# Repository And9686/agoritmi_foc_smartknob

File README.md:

# Algoritmi SmartKnob DevKit
## Motivation
This repository intends to achieve a development kit for a SmartKnob like the one from scottbez and allow it to be compatible with any microcontroller with dedicated firmware adaptable to any board. This DevKit design is inspired by NanoFoc DevKit by KatBinaris.

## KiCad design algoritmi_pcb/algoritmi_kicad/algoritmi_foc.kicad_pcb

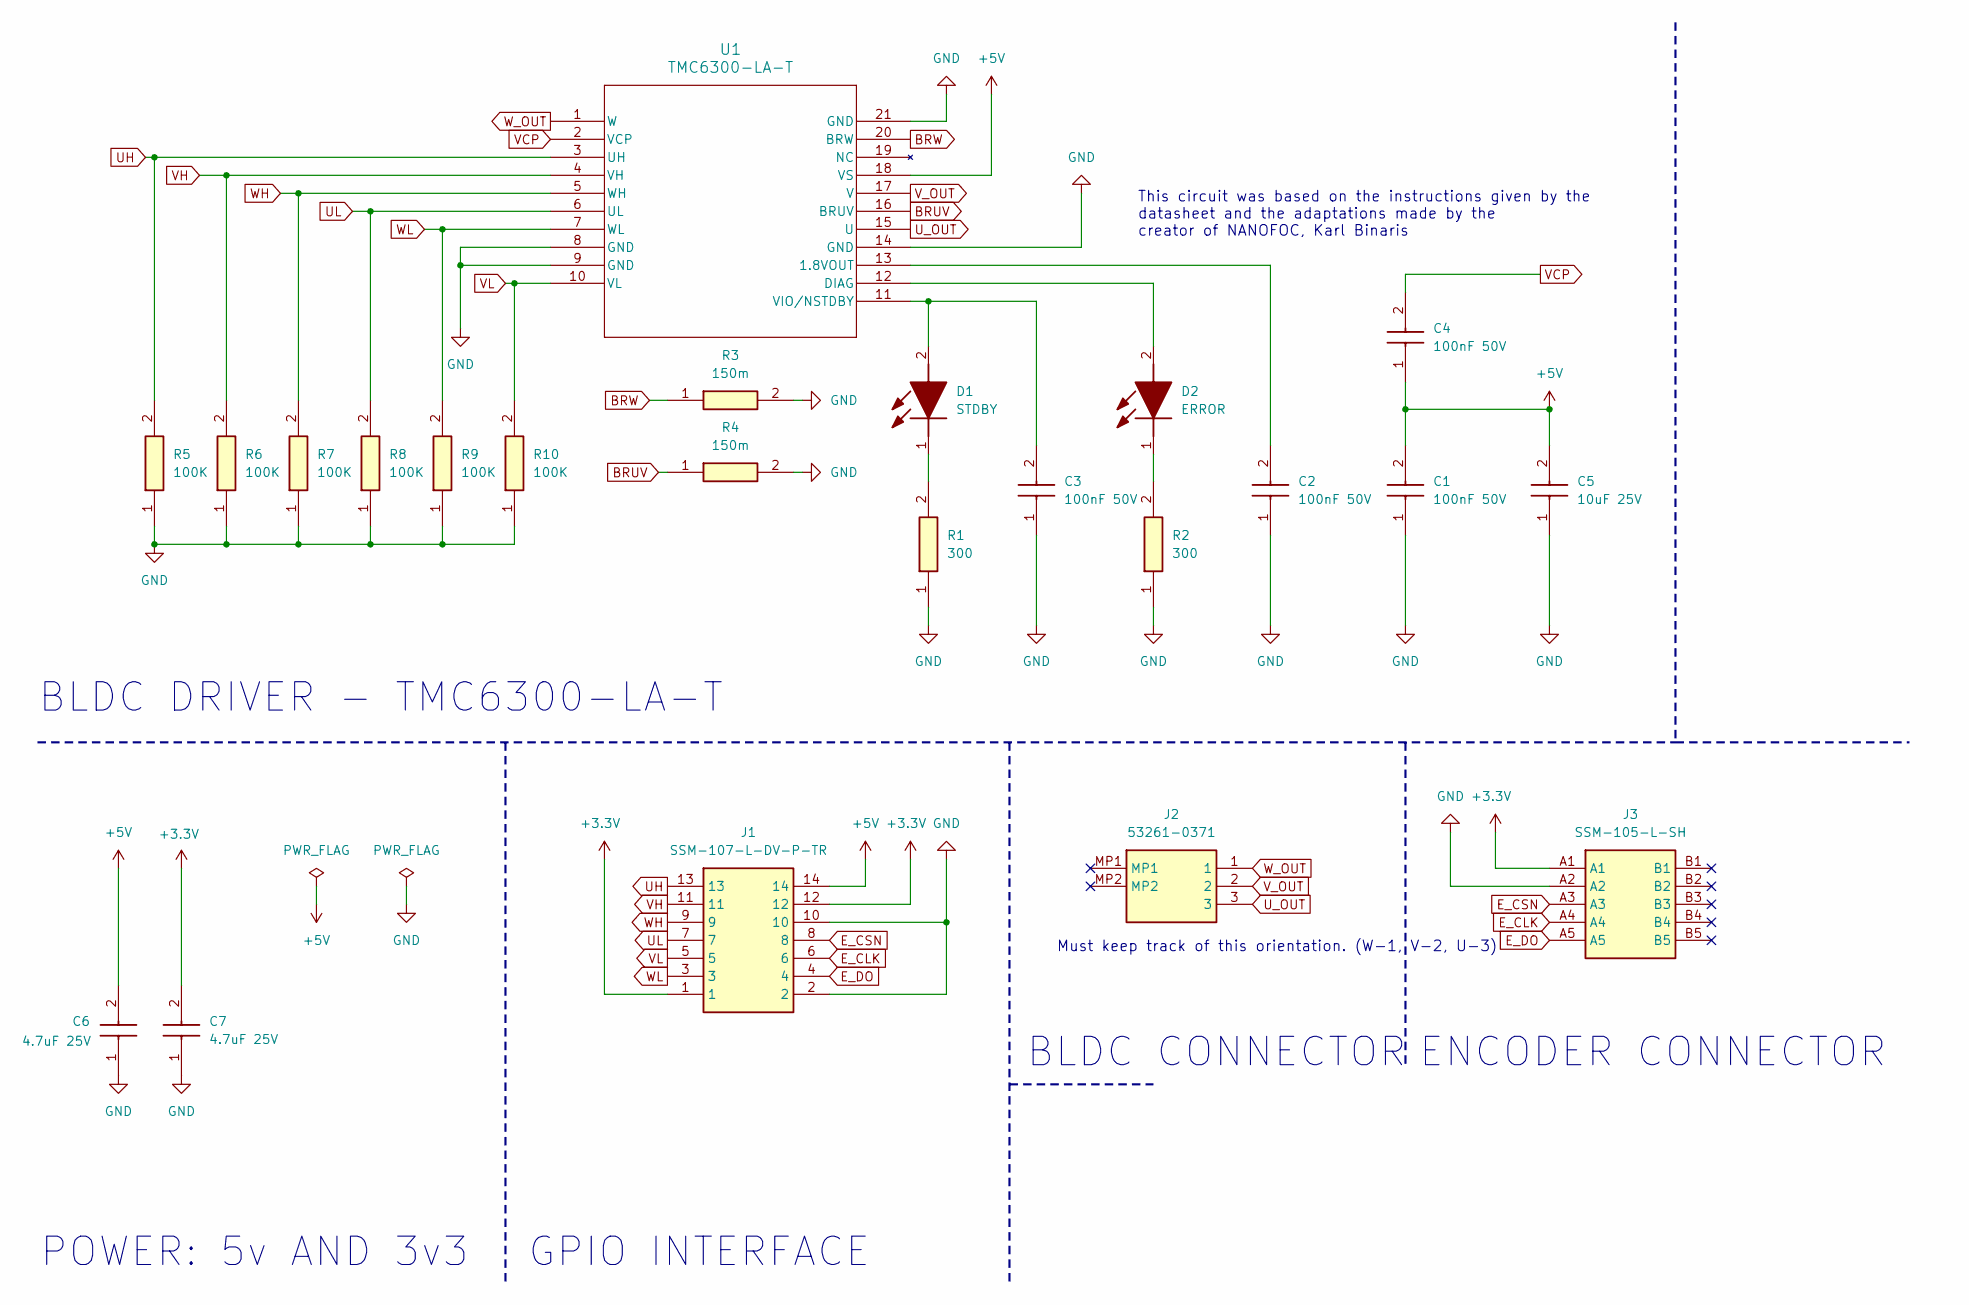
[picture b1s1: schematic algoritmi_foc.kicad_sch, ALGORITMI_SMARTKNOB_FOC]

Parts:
C1, C2, C3, C4: 100nF 50V; C_0201_0603Metric; Mouser Part Number 187-CL10B104KB8NNWC
C5: 10uF 25V; C_0805_2012Metric; Mouser Part Number 187-CL21A106KAYNNNE
C6, C7: 4.7uF 25V; C_0805_2012Metric; Mouser Part Number 81-GCM21BC71E475KE6K
D1: STDBY; LED_0603_1608Metric; Mouser Part Number 755-SML-D12M8WT86
D2: ERROR; LED_0603_1608Metric; Mouser Part Number 755-SML-D12M8WT86
J1: SSM-107-L-DV-P-TR; SSM-107-XXX-DV-P-TR; Mouser Part Number 200-SSM107LDVPTR
J2: 53261-0371; 532610371; Mouser Part Number 538-53261-0371
J3: SSM-105-L-SH; SSM105LSH; Mouser Part Number 200-SSM105LSH
R1, R2: 300; R_0201_0603Metric; Mouser Part Number 667-ERJ-UP3F3000V
R3, R4: 150m; R_1206_3216Metric; Manufacturer_Part_Number UR73VH2BTTDR150F
R5, R6, R7, R8, R9, R10: 100K; R_0201_0603Metric; Mouser Part Number 652-CMP0603-FX-1003L
U1: TMC6300-LA-T; QFN40P300X300X90-21N

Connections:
+3.3V: C7.2, J1.1, J1.12, J3.A1
+5V: C1.2, C4.1, C5.2, C6.2, J1.14, U1.18 (VS)
BRUV: R4.1, U1.16 (BRUV)
BRW: R3.1, U1.20 (BRW)
E_CLK: J1.6, J3.A4
E_CSN: J1.8, J3.A3
E_DO: J1.4, J3.A5
GND: C1.1, C2.1, C3.1, C5.1, C6.1, C7.1, J1.2, J1.10, J3.A2, R1.1, R2.1, R3.2, R4.2, R5.1, R6.1, R7.1, R8.1, R9.1, R10.1, U1.8 (GND), U1.9 (GND), U1.14 (GND), U1.21 (GND)
unnamed 8: C3.2, D1.2 (A), U1.11 (VIO/NSTDBY); also elsewhere on the board
unnamed 9: D1.1 (K), R1.2; also elsewhere on the board
unnamed 10: D2.2 (A), U1.12 (DIAG); also elsewhere on the board
unnamed 11: D2.1 (K), R2.2; also elsewhere on the board
unnamed: C2.2, U1.13 (1.8VOUT)
UH: J1.13, R5.2, U1.3 (UH)
UL: J1.7, R8.2, U1.6 (UL)
U_OUT: J2.3, U1.15 (U)
VCP: C4.2, U1.2 (VCP)
VH: J1.11, R6.2, U1.4 (VH)
VL: J1.5, R10.2, U1.10 (VL)
V_OUT: J2.2, U1.17 (V)
WH: J1.9, R7.2, U1.5 (WH)
WL: J1.3, R9.2, U1.7 (WL)
W_OUT: J2.1, U1.1 (W)

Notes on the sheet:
Must keep track of this orientation. (W-1, V-2, U-3)
ENCODER CONNECTOR
GPIO INTERFACE
BLDC DRIVER - TMC6300-LA-T
BLDC CONNECTOR
This circuit was based on the instructions given by the datasheet and the adaptations made by the creator of NANOFOC, Karl Binaris
POWER: 5v AND 3v3

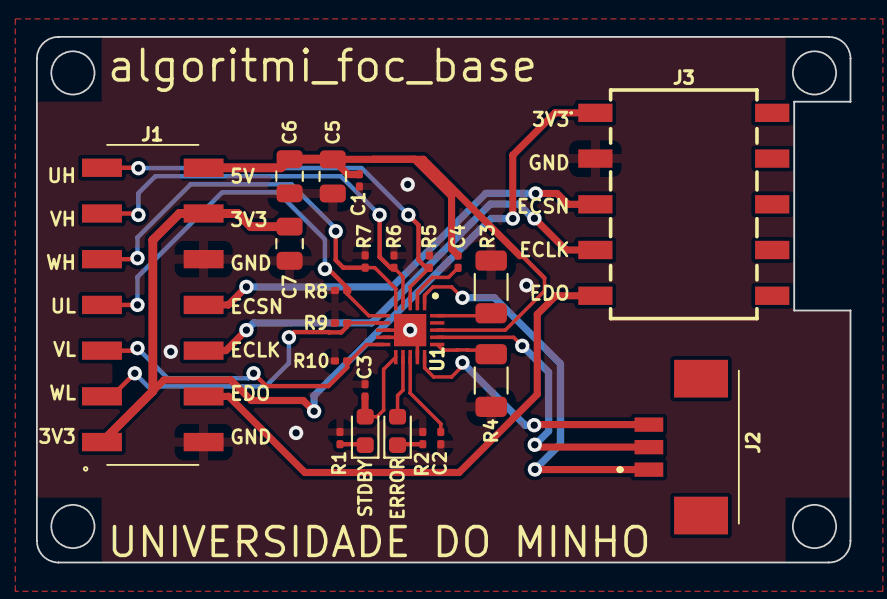
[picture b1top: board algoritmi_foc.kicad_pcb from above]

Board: 2 copper layers, 45.2 x 29.2 mm, 23 parts (0 on the bottom side), 23 nets.

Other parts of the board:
ERROR: ERROR; LED_0603_1608Metric
STDBY: STDBY; LED_0603_1608Metric

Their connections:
unnamed 8: STDBY.2 (A); also elsewhere on the board
unnamed 9: STDBY.1 (K); also elsewhere on the board
unnamed 10: ERROR.2 (A); also elsewhere on the board
unnamed 11: ERROR.1 (K); also elsewhere on the board

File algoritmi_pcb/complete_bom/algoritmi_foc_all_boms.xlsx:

Reference | Value | Datasheet | Footprint | Qty | DNP | Manufacturer_Name | Manufacturer_Part_Number | Mouser Part Number
C1,C2,C3,C4 | 100nF 50V | http://www.samsungsem.com/kr/support/product-search/mlcc/CL1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 | Capacitor_SMD:C_0201_0603Metric | 4 |  | SAMSUNG | CL10B104KB8NNWC | 187-CL10B104KB8NNWC
C5 | 10uF 25V | https://datasheet.datasheetarchive.com/originals/distributor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 | Capacitor_SMD:C_0805_2012Metric | 1 |  | SAMSUNG | CL21A106KAYNNNE | 187-CL21A106KAYNNNE
C6,C7 | 4.7uF 25V | https://psearch.en.murata.com/capacitor/product/GCM21BC71E47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 | Capacitor_SMD:C_0805_2012Metric | 2 |  | Murata Electronics | GCM21BC71E475KE36K | 81-GCM21BC71E475KE6K
D1,D2 | -- mixed values -- | https://datasheet.datasheetarchive.com/originals/distributor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 | LED_SMD:LED_0603_1608Metric | 2 |  | ROHM Semiconductor | SML-D12M8WT86 | 755-SML-D12M8WT86
J1 | SSM-107-L-DV-P-TR | http://suddendocs.samtec.com/prints/ssm-1xx-xxx-dv-xx-xx-xxx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 | SSM-107-XXX-DV-P-TR | 1 |  | SAMTEC | SSM-107-L-DV-P-TR | 200-SSM107LDVPTR
J2 | 53261-0371 |  | 532610371 | 1 |  | Molex | 53261-0371 | 538-53261-0371
J3 | SSM-105-L-SH | https://componentsearchengine.com/Datasheets/1/SSM-105-L-SH.pdf | SSM105LSH | 1 |  | SAMTEC | SSM-105-L-SH | 200-SSM105LSH
R1,R2 | 300ohm | https://industrial.panasonic.com/cdbs/www-data/pdf/RDP0000/A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 | Resistor_SMD:R_0201_0603Metric | 2 |  | Panasonic | ERJ-UP3F3000V | 667-ERJ-UP3F3000V
R3,R4 | 150m | https://www.koaspeer.com/pdfs/UR73V.pdf | Resistor_SMD:R_1206_3216Metric | 2 |  | KOA Speer | UR73VH2BTTDR150F | 660-UR73VH2BTTDR150F
R5,R6,R7,R8,R9,R10 | 100K | https://www.mouser.co.uk/datasheet/2/54/Bourns_CMP_Datasheet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 | Resistor_SMD:R_0201_0603Metric | 6 |  | Bourns | CMP0603-FX-1003ELF | 652-CMP0603-FX-1003L
U1 | TMC6300-LA-T | TMC6300-LA-T | SamacSys_Parts:QFN40P300X300X90-21N | 1 |  | ADI Trinamic | TMC6300-LA-T | 700-TMC6300-LA-T

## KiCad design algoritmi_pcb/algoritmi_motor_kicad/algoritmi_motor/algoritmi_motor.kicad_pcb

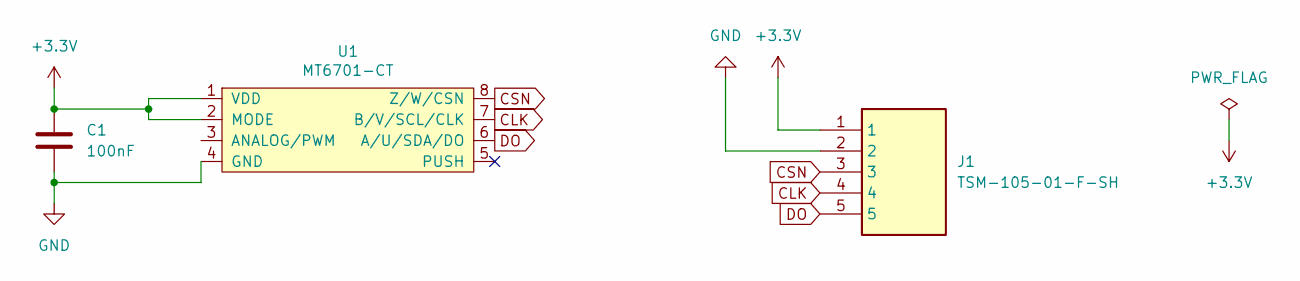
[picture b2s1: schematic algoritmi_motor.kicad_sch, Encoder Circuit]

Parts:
C1: 100nF; C_0201_0603Metric
J1: TSM-105-01-F-SH; TSM-105-YY-ZZZ-SH; Mouser Part Number 200-TSM10501FSH
U1: MT6701-CT; SOIC-8_3.9x4.9mm_P1.27mm; LCSC C2856764, or C3003196

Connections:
+3.3V: C1.1, J1.1, U1.1 (VDD), U1.2 (MODE)
CLK: J1.4, U1.7 (B/V/SCL/CLK)
CSN: J1.3, U1.8 (Z/W/CSN)
DO: J1.5, U1.6 (A/U/SDA/DO)
GND: C1.2, J1.2, U1.4 (GND)

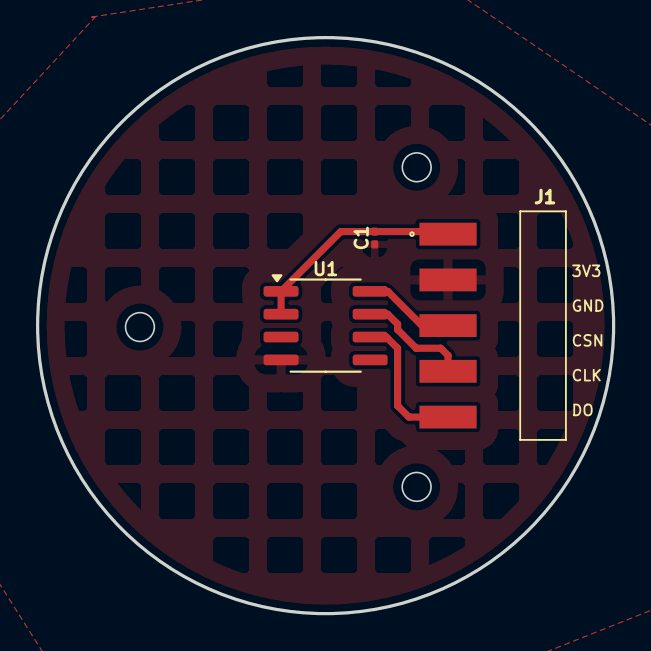
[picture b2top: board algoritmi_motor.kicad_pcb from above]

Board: 2 copper layers, 32.0 x 32.0 mm, 3 parts (0 on the bottom side), 5 nets.

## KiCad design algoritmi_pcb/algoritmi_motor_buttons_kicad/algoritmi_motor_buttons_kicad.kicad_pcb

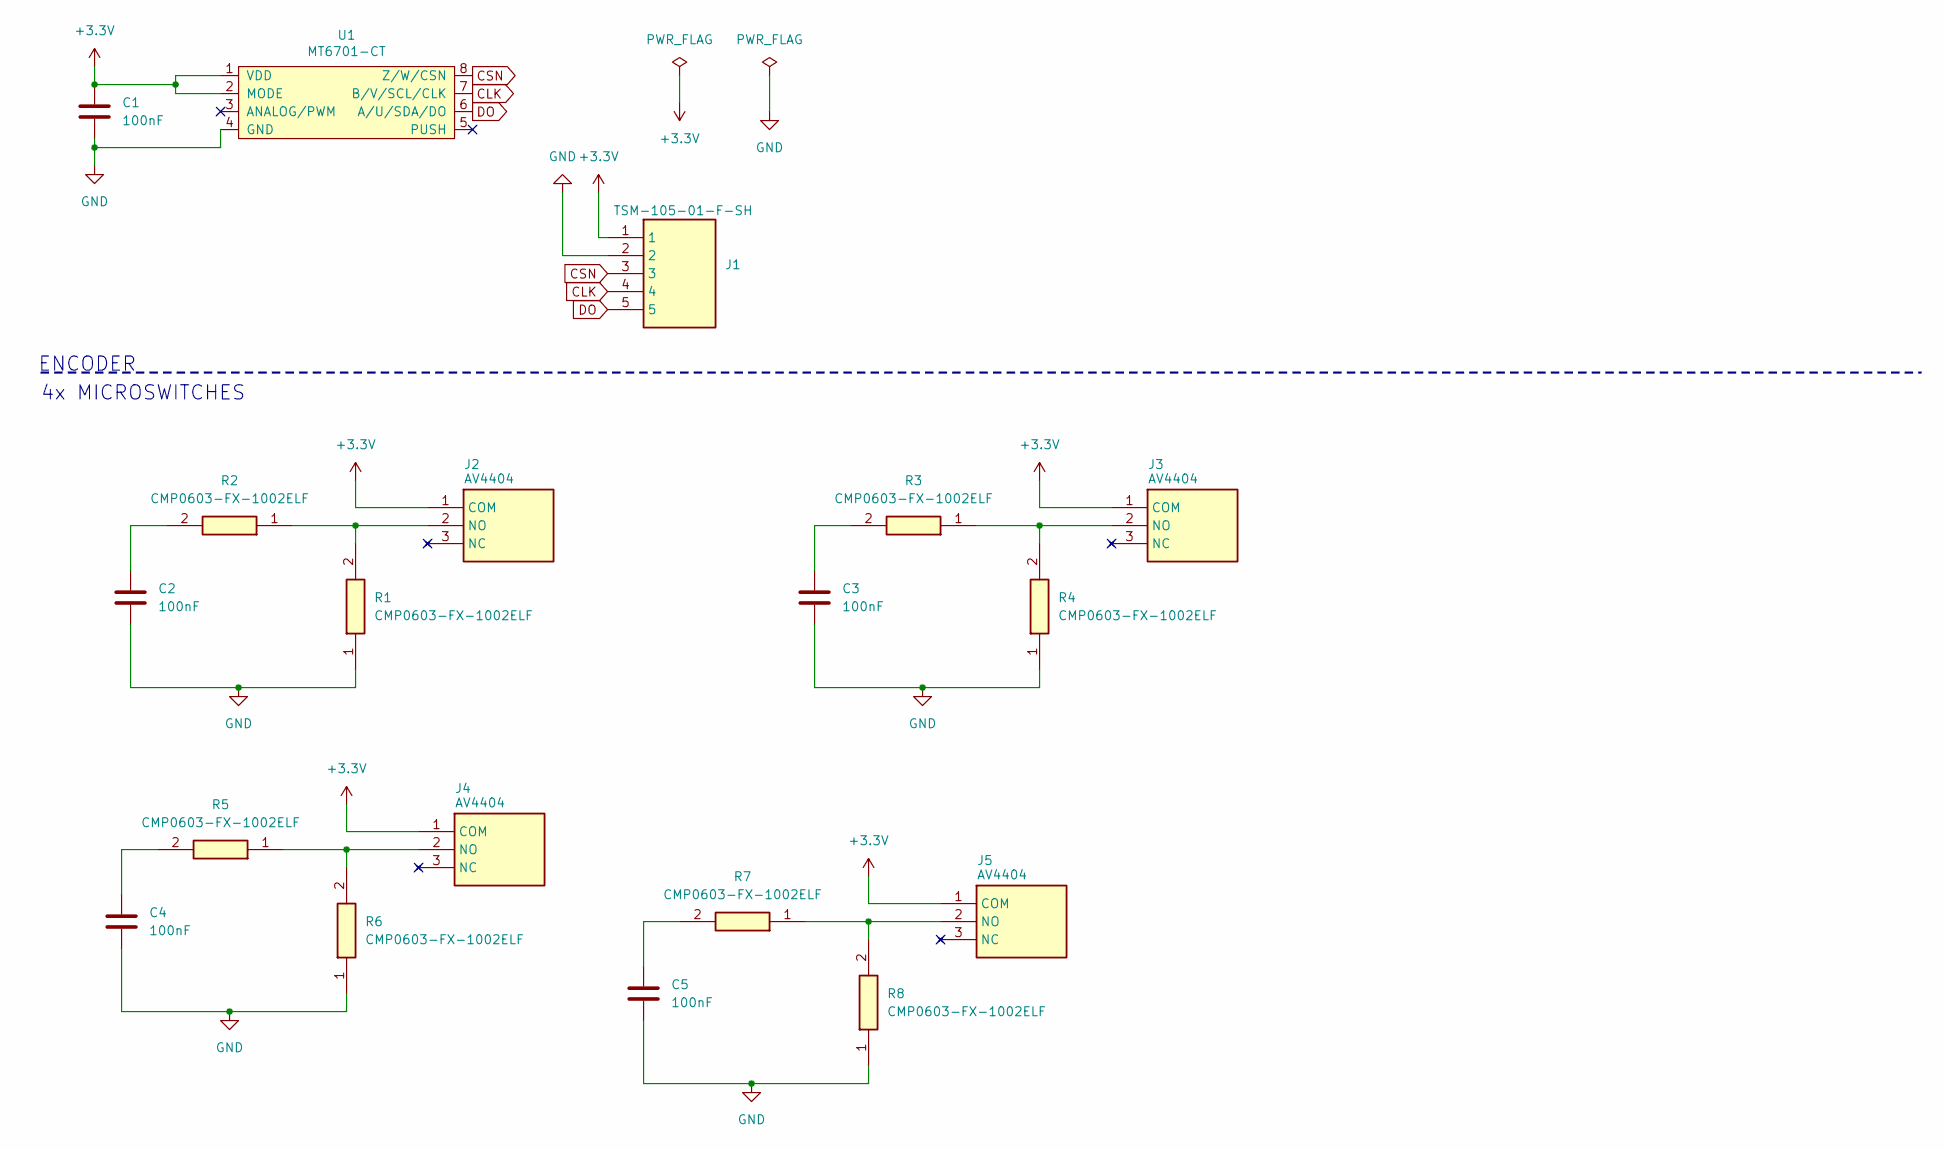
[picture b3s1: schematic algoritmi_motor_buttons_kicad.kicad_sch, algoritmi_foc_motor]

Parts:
C1, C2, C3, C4, C5: 100nF; C_0201_0603Metric
J1: TSM-105-01-F-SH; TSM-105-YY-ZZZ-SH; Mouser Part Number 200-TSM10501FSH
J2, J3, J4, J5: AV4404; Manufacturer_Part_Number AV4404
R1, R2, R3, R4, R5, R6, R7, R8: CMP0603-FX-1002ELF; RESC1608X55N; Mouser Part Number 652-CMP0603-FX-1002L
U1: MT6701-CT; SOIC-8_3.9x4.9mm_P1.27mm; LCSC C2856764 ou C3003196

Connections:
+3.3V: C1.1, J1.1, J2.1 (COM), J3.1 (COM), J4.1 (COM), J5.1 (COM), U1.1 (VDD), U1.2 (MODE)
CLK: J1.4, U1.7 (B/V/SCL/CLK)
CSN: J1.3, U1.8 (Z/W/CSN)
DO: J1.5, U1.6 (A/U/SDA/DO)
GND: C1.2, C2.2, C3.2, C4.2, C5.2, J1.2, R1.1, R4.1, R6.1, R8.1, U1.4 (GND)
unnamed: C2.1, R2.2
unnamed: C3.1, R3.2
unnamed: C4.1, R5.2
unnamed: C5.1, R7.2
unnamed: J2.2 (NO), R1.2, R2.1
unnamed: J3.2 (NO), R3.1, R4.2
unnamed: J4.2 (NO), R5.1, R6.2
unnamed: J5.2 (NO), R7.1, R8.2

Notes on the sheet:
4x MICROSWITCHES
ENCODER

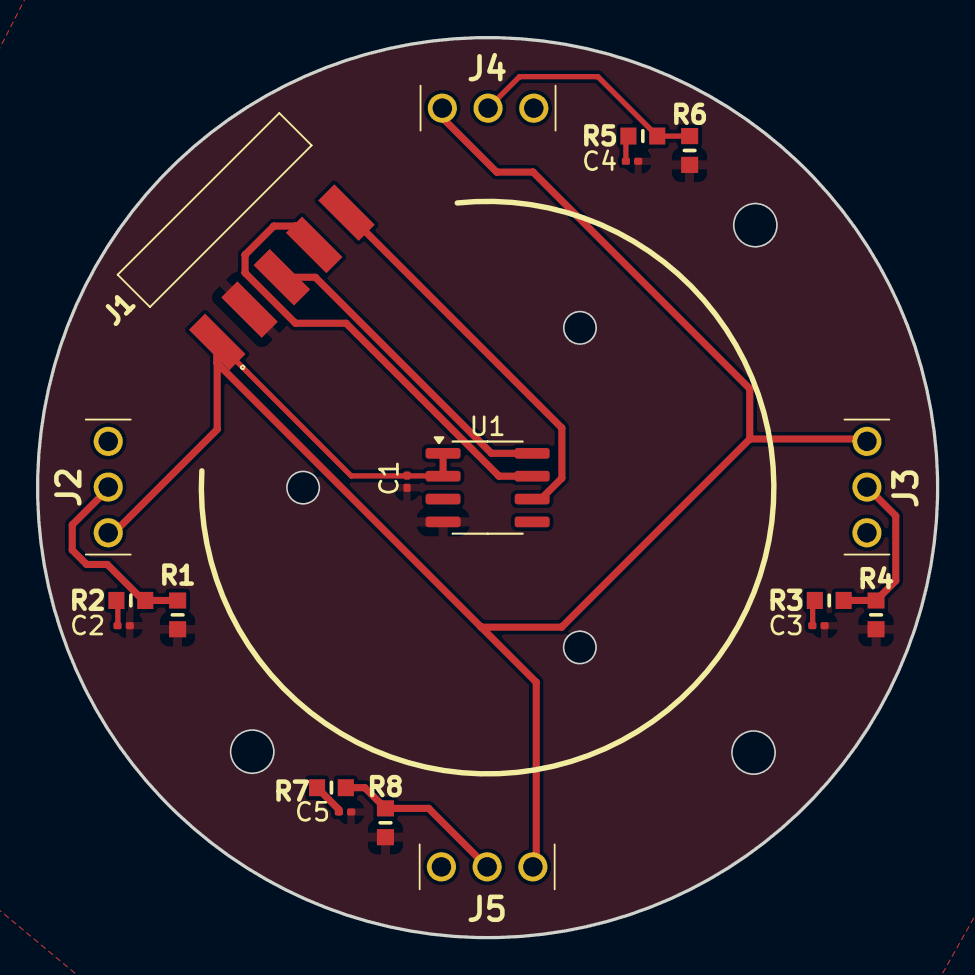
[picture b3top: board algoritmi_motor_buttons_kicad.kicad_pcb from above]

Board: 2 copper layers, 50.0 x 50.0 mm, 19 parts (0 on the bottom side), 13 nets.

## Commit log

2024-07-22 Motivation Update README.md
2024-07-22 Work Till Now
    PCB schematics unfinished
2024-07-23 Updates to the schematics
2024-07-24 Schematics: Added Power and Encoder
2024-07-24 Component Footprints Added
2024-07-25 Final Schematics and started PCB design
2024-07-25 Components Update
2024-07-26 Update PCB and Design
    Design: added the connector for the motor.
    PCB: added some constraints and essentially connected all the components to the TMC6300-LA-T.
2024-07-26 Components Update
    Added the component for the Motor connector.
2024-07-29 More PCB and Schematics Design
    Also added components to the library.
2024-07-30 PCB v0 Finished
    PCB design ended, version 0
2024-07-31 added gerber and drill files
2024-07-31 updated stuff
2024-09-02 my laptop version updated
2024-09-02 finished version_1
    doesn't have the presure sensitive part
2024-09-02 extra updates version 1
2024-09-05 New updates
2024-09-05 recovery of bridges
2024-09-05 adding the presure sensitive click pcb
    I forgot to put it in the right position :)
2024-09-06 updated positioning of presure sensors
    NOTE: the GND on the presure sensor circuit is not connected to the GND of the whole circuit.
2024-09-06 updates
    Just opened the file and closed, the kicad always generates autosaves.
2024-09-06 updates
    updates to the pcb
2024-09-09 finished base pcb
    in the last meeting with professor, we decided to separate the smartknob into 3 pcb's, one that contains the encoder and the motor, the other that contains the connectors and motor driver, and anothe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
2024-09-09 some changes to schematics
2024-09-10 updates to the schematics
    Updates regarding the schematics: removing power circuits and rechanging some labels and names.
2024-09-12 Changed the base pcb and started motor pcb
    The motor pcb is almost finished, just needs to get the encoder centered in the middle.
2024-09-13 All 3 PCBs done
    There's still work left: generate all the BOMs and re-check all the circuits and see if nothing is wrong.
2024-09-17 generated BOMs and Gerbers
2024-09-23 Updated Gerbers Base PCB
2025-01-10 Updates of 3d models
2025-01-10 added all updated firmware
    Forked from smartknob: added bluetooth module, modified some interface functionality, will remove current display task and add one for ILI9341 touchscreen display.
2025-01-10 Removed unnecessary files
2025-01-29 major changes to the code
    Implemented the ILI9341 display with already a whole menu interacting with the android bluetooth app.
    Solved some issues regarding the bluetooth communication where the heap was being currupted because of using strings and not alocating memory correctly.
2025-02-09 visual diagramas
2025-02-11 update to diagrams
    Updated the lifeline UML diagram.
2025-03-21 update firmware and other stuff
2025-03-21 correction
